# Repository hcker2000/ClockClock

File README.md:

# ClockClock
---
## Features
* Daylight alarm via led strip will start to brighten 15 minutes before scheduled alarm time
* Bed Shaker will start 1 minute before scheduled alarm time
* Buzzer will start at scheduled alarm time
* Alarm finishes one minute after scheduled alarm time
* WiFi setup/config
## Hardware
Currently this is being developed on a wemos D1 and a 128x64 OLED display. I have mounted the Voltage Regulator on headers to give it some breathing room. Please ignore the flux in the pictures.

### Libraries
* Time is kept in sync via NTP lib at [https://github.com/PaulStoffregen/Time](https://github.com/PaulStoffregen/Time)
* Timezone/Daylight savings time are handled via TimeZone lib at [https://github.com/JChristensen/Timezone](https://github.com/JChristensen/Timezone)
* WiFi setup/config is provided by the amazing WiFi Config lib at [https://github.com/tzapu/WiFiManager](https://github.com/tzapu/WiFiManager)
* OLED Display is provided by [https://github.com/stblassitude/Adafruit_SSD1306_Wemos_OLED](https://github.com/stblassitude/Adafruit_SSD1306_Wemos_OLED)

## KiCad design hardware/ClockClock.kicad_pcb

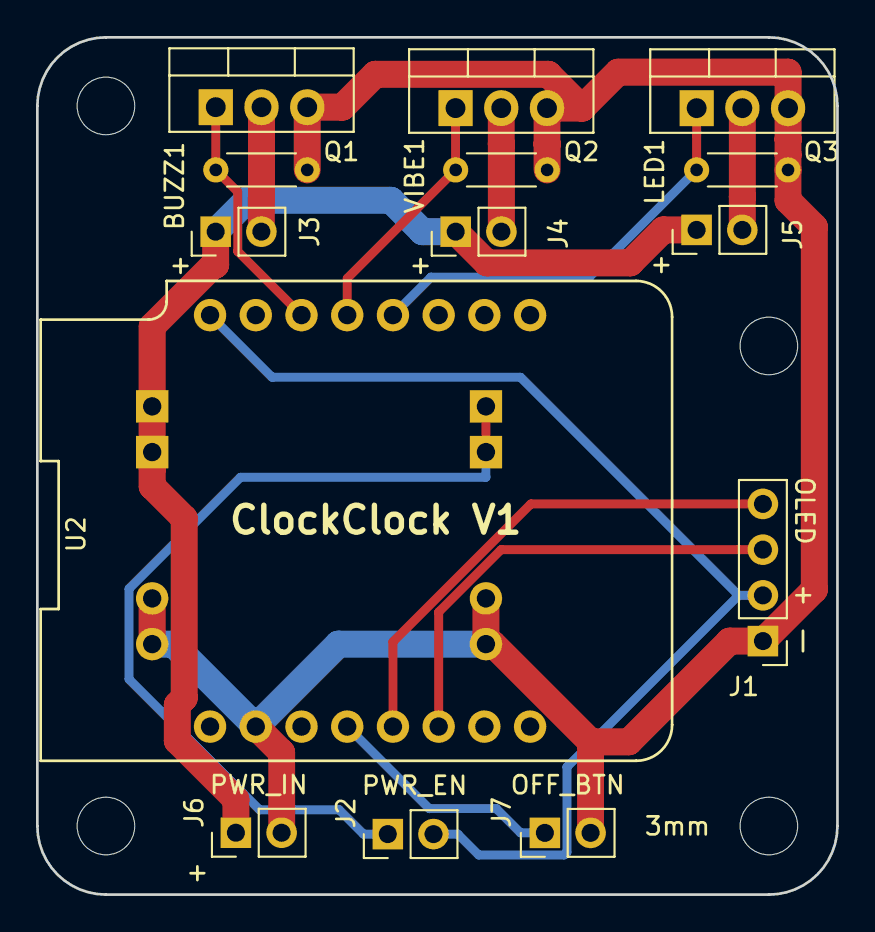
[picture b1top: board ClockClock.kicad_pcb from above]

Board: 2 copper layers, 44.5 x 47.6 mm, 19 parts (1 on the bottom side), 13 nets.

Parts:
BUZZ1: 10k; R_Axial_DIN0204_L3.6mm_D1.6mm_P5.08mm_Horizontal
J1: OLED; PinHeader_1x04_P2.54mm_Vertical
J2: PWR_EN; PinHeader_1x02_P2.54mm_Vertical
J3: BUZZ_CON; PinHeader_1x02_P2.54mm_Vertical
J4: VIBE_CON; PinHeader_1x02_P2.54mm_Vertical
J5: LED_CON; PinHeader_1x02_P2.54mm_Vertical
J6: +12V_IN; PinHeader_1x02_P2.54mm_Vertical
J7: OFF_BTN; PinHeader_1x02_P2.54mm_Vertical
LED1: 10k; R_Axial_DIN0204_L3.6mm_D1.6mm_P5.08mm_Horizontal
Q1, Q2, Q3: IRLZ44N; TO-220-3_Vertical
U1: 3a_dcdc_vreg_board; 8_pin_header_mount
U2: WeMos_mini; wemos-d1-mini-with-pin-header-and-connector
VIBE1: 10k; R_Axial_DIN0204_L3.6mm_D1.6mm_P5.08mm_Horizontal
m1, m2, m3, m4: MountingHole_3.2mm_M3

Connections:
+12V: J3.1, J4.1, J5.1, J6.1, U1.5, U1.7
GND: BUZZ1.2, J1.1, J6.2, J7.2, LED1.2, Q1.3, Q2.3, Q3.3, U1.1, U1.2, U1.3, U1.4, U2.2, VIBE1.2
unnamed: BUZZ1.1, Q1.1, U2.14
unnamed: J1.2, J2.2, U2.16
unnamed: J1.3, U2.6
unnamed: J1.4, U2.5
unnamed: J2.1, U1.6, U1.8
unnamed: J3.2, Q1.2
unnamed: J4.2, Q2.2
unnamed: J5.2, Q3.2
unnamed: J7.1, U2.4
unnamed: LED1.1, Q3.1, U2.12
unnamed: Q2.1, U2.13, VIBE1.1

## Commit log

2018-09-06 Initial
2018-09-06 ignore vs code settings
2018-09-06 Delete settings.json
    not needed
2018-09-06 updated readme to reflect current dev setup
2018-09-06 cleaning up
2018-09-06 more formating
2018-09-06 formating
2018-09-11 updated pin asignments and started hardware
2018-09-12 Getting board design ready for printing
2018-09-13 directory clean up and better more finalized layout
2018-09-13 added code to handle an off button
2018-09-13 Finalized board layout and added some pictures to the info
2018-09-24 Updated some labels on the 3 amp voltage regulator
2018-09-24 quick readme update
2018-09-25 Updated readme with a link to the oled library that was used
2018-09-25 updated readme with some pictures of the prototypes display
2018-10-04 Updated pcb image to include distances between mounting holes
2018-10-04 Missed saving the actual kicad pcb file
2018-10-10 Added soldered board images
2018-11-06 fixed a spelling mistake
2018-11-06 Fixed a bug where the time zone was not being setup correctly
2018-11-07 tiny bit of code cleanup
2018-11-07 Added code to invert the oled as soon as the alarm starts it run.
2018-11-08 Fixed a spelling mistake and lowered the debounce from 500 to 100ms
2019-08-13 Added .pio to .gitignore
